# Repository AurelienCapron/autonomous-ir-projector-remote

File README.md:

# Télécommande Infrarouge Autonome pour Vidéoprojecteurs (Projet 32)

Conception matérielle (prototypage sur Arduino Uno puis PCB sur mesure sous KiCad 9), rétro-ingénierie de protocole infrarouge (standard NEC 38 kHz) et développement logiciel embarqué (MicroPython & C++) d'un boîtier autonome destiné à éteindre automatiquement les vidéoprojecteurs de la salle des conseils de **Grenoble INP - Phelma** lorsqu'elle est inoccupée. Ce système prévient l'usure prématurée des lampes (estimée à 1 250 h/an d'allumage inutile, soit 33 % de leur durée de vie) et réduit la consommation énergétique du bâtiment.

* **[Consulter le rapport technique du projet (PDF)](docs/project_report.pdf)**
* **[Consulter le support de soutenance technique (PDF)](docs/presentation_slides.pdf)**
* **[Consulter le schéma électrique du prototype initial (PDF)](docs/arduino_prototype_schematic.pdf)**
* **[Voir la vidéo de démonstration du prototype en salle des conseils](assets/autonomous_remote_demo.mp4?raw=true)**

---

## Sommaire
1. [Aperçu matériel : du prototype au produit final](#aperçu-matériel--du-prototype-au-produit-final)
2. [Contexte et cahier des charges (SysML)](#contexte-et-cahier-des-charges-sysml)
3. [Architecture matérielle et carte PCB (KiCad 9)](#architecture-matérielle-et-carte-pcb-kicad-9)
4. [Rétro-ingénierie du protocole NEC et firmware embarqué](#rétro-ingénierie-du-protocole-nec-et-firmware-embarqué)
5. [Conception mécanique et intégration du boîtier](#conception-mécanique-et-intégration-du-boîtier)
6. [Structure du dépôt](#structure-du-dépôt)
7. [Auteurs et encadrement](#auteurs-et-encadrement)

---

## Aperçu matériel : du prototype au produit final

| Phase 1 : Prototypage sur breadboard (Arduino Uno) | Phase 2 : Conception PCB sur mesure (KiCad 9 — v1.2) |
| :---: | :---: |
|  |  |
| *Câblage initial sur plaque d'essai : Arduino Uno, 2 capteurs PIR, 4 LDR (`A0`–`A3`), récepteur et LED IR* | *Carte finale double face accueillant le Raspberry Pi Pico 2WH, l'étage LDO 5V et les connecteurs dédiés* |

| Assemblage et soudure au laboratoire | Câblage interne dans le boîtier | Prototype final assemblé et testé |
| :---: | :---: | :---: |
|  |  |  |

---

## Contexte et cahier des charges (SysML)

À l'issue des réunions en salle des conseils, les vidéoprojecteurs restent fréquemment allumés toute la nuit (environ 2 fois par semaine, soit $1\,250\text{ h/an}$ sur une durée de vie totale de lampe de $3\,000$ à $4\,000\text{ h}$). Le système conçu répond à trois niveaux d'exigences fonctionnelles :
1. **Détection de l'état réel des vidéoprojecteurs :** Mesure directe de la tension sur les sorties **VGA** (`VGA1`, `VGA2`) couplée à des photorésistances (`PGM1201`) afin de ne commander l'extinction que si l'appareil ciblé est effectivement sous tension.
2. **Surveillance multi-capteurs de l'occupation :** Fusion des informations issues d'un capteur de mouvement infrarouge passif (`SBC-PIR`), d'un radar de présence à ondes millimétriques (`mmWave Gravity SEN0609`) et d'un détecteur acoustique (`SEN-14262`).
3. **Extinction automatique et mode *Sniffer* d'apprentissage :** Émission d'une salve infrarouge d'extinction après $1\text{h}30$ ($5\,400\text{ s}$) d'inactivité ou en cas de surchauffe/luminosité excessive, et possibilité de cloner à la volée une nouvelle télécommande par simple appui long (3 secondes) sur le bouton d'apprentissage (`GPIO19`).

---

## Architecture matérielle et carte PCB (KiCad 9)

### Brochage de la carte électronique (Version 1.2)

La carte électronique double face ($135 \times 130\text{ mm}$) intègre un étage de régulation linéaire **5V** (`TLV1117-50` alimenté en 12V DC via `J1`) et centralise l'ensemble des capteurs et actionneurs autour du microcontrôleur **Raspberry Pi Pico 2WH** :

| Connecteur PCB | Signal / Label | Broche MCU | Rôle fonctionnel |
|---|---|---|---|
| **`J_VGA1` / `J_VGA2`** | `VGA1` / `VGA2` | `GPIO3` / `GPIO2` | Lecture de l'état sous tension des vidéoprojecteurs 1 et 2 via leurs ports VGA. |
| **`J_Photoresistance1/2`** | `ADC0` / `ADC1` | `GPIO26` / `GPIO27` | Mesure analogique de luminosité (`PGM1201`) avec pont diviseur $10\text{ k}\Omega$ (`R5`, `R6`). |
| **`RV1`** | `ADC2` | `GPIO28` | Potentiomètre CMS Vishay `TS53YL` ($100\text{ k}\Omega$) d'ajustement dynamique du seuil. |
| **`J_DETECTEUR_MOUVEMENT1`** | `SIG` | `GPIO16` | Entrée numérique du capteur de mouvement infrarouge passif (`SBC-PIR`). |
| **`J_DETECTEUR_PRESENCE1`** | `VOUT` | `GPIO17` | Entrée numérique du capteur de présence radar mmWave (`SEN0609`). |
| **`J_CAPTEUR_SONORE1/2`** | `ENVELOPE` / `GATE` | `GPIO20` / `GPIO21` | Acquisition de l'enveloppe acoustique et du seuil binaire (`SEN-14262`). |
| **`J_EMETTEUR1` / `2`** | `EMETTEUR1` / `2` | `GPIO7` / `GPIO14` | Commande PWM 38 kHz des 2 émetteurs IR (`GT1087`) via résistances $220\ \Omega$ (`R3`, `R4`). |
| **`J_RECEPTEUR1`** | `S_OUT` | `GPIO18` | Réception et apprentissage (*Sniffer*) de trames infrarouges externes (`GT1089`). |
| **`J_Bouton1`** | `BOUTON` | `GPIO19` | Bouton poussoir (`R1381R`, `PULL_UP`) activant le mode apprentissage après 3 s d'appui. |
| **`J_LED1` / `J_LED2`** | `Net-(GPIO0/1)` | `GPIO0` / `GPIO1` | LED témoins en façade (Présence détectée sur `GPIO0`, Projecteur allumé sur `GPIO1`). |

### Nomenclature matérielle (BOM)

| Composant | Référence | Quantité | Fonction |
|---|---|---|---|
| Microcontrôleur | `Raspberry Pi Pico 2WH` (`SC1634`) | 1 | Unité centrale de traitement, PWM 38 kHz et machine d'état |
| Régulateur LDO 5V | `TLV1117-50` (SOT-223) | 1 | Régulation 12V → 5V (`VCC`) avec condensateurs CMS $10\ \mu\text{F}$ (`C1`, `C2`) |
| Détecteur sonore | `SEN-14262` | 1 | Surveillance de l'activité sonore dans la salle des conseils |
| Radar de présence | `mmWave Gravity SEN0609` | 1 | Détection fine de présence humaine statique ou en mouvement |
| Capteur PIR | `SBC-PIR` | 1 | Détection de mouvement thermique dans la salle |
| Photorésistances | `PGM1201` | 4 | Détection optique complémentaire et sécurité de surchauffe |
| Émetteurs IR | `GT1087` | 2 | Émission directionnelle des trames d'extinction à 38 kHz |
| Récepteur IR | `GT1089` | 1 | Capture et clonage du signal de la télécommande d'origine |
| Bouton poussoir | `R1381R` | 1 | Déclenchement manuel du mode d'apprentissage infrarouge |

---

## Rétro-ingénierie du protocole NEC et firmware embarqué

### 1. Identification et décodage de la trame à l'oscilloscope
Le signal émis par la télécommande d'origine face au récepteur `GT1089` a été capturé à l'oscilloscope numérique **Tektronix** et décodé via un banc Arduino Uno (`firmware/arduino_ir_receiver`), révélant une modulation **NEC** sur porteuse à **38 kHz** de valeur hexadécimale brute **`0x6F905583`** (soit les 4 octets `0x83`, `0x55`, `0x90`, `0x6F` transmis LSB-first) :

* **En-tête de synchronisation (AGC Burst) :** Impulsion modulée de $9\text{ ms}$ (`mark(9000)`) suivie d'un silence de $4,5\text{ ms}$ (`space(4500)`).
* **Bit logique `0` :** Impulsion de $562\ \mu\text{s}$ suivie d'un silence de $562\ \mu\text{s}$ (durée totale : $1,125\text{ ms}$).
* **Bit logique `1` :** Impulsion de $562\ \mu\text{s}$ suivie d'un silence long de $1,675\ \text{ms}$ (durée totale : $2,25\text{ ms}$).

| Principe temporel du protocole NEC | Capture de la trame IR à l'oscilloscope Tektronix |
| :---: | :---: |
|  |  |

### 2. Synthèse PWM 38 kHz et mode *Sniffer* sous MicroPython (`firmware/pico_main/main.py`)
Le firmware principal embarqué sur le **Raspberry Pi Pico 2WH** pilote simultanément les deux émetteurs IR (`GPIO7` et `GPIO14`) via les générateurs PWM matériels cadencés à $38\text{ kHz}$ (rapport cyclique de 50 %, `duty_u16(32768)`) :
* **Triple tir d'extinction (`envoyer_code_nec_universel()`) :** Envoie 3 trames NEC consécutives espacées de $500\text{ ms}$ pour garantir la prise en compte de l'extinction (y compris sur les projecteurs exigeant une double confirmation).
* **Mode d'apprentissage universel (`lancer_mode_apprentissage()`) :** Un appui de plus de 3 secondes sur le bouton `GPIO19` place le boîtier en écoute sur le récepteur `GT1089` (`GPIO18`), mesure à la microseconde les 67 fronts successifs (`time.ticks_us()`), discrimine les bits `1` ($> 1\,200\ \mu\text{s}$) et `0`, et met à jour dynamiquement en mémoire les 4 octets `NEC_B1` à `NEC_B4`.

---

## Conception mécanique et intégration du boîtier

Pour protéger la carte électronique de la poussière dans le faux plafond tout en intégrant les passages de câbles et l'interface utilisateur :
1. **Modélisation 3D initiale (CAO 3D) :** Conception d'un boîtier perforé et de son couvercle à poignée.
2. **Boîtier en bois découpé au laser (solution retenue) :** Conception d'un boîtier assemblé à créneaux ($14 \times 15,5 \times 10\text{ cm}$) généré via `boxes.py`, adapté en CAO 2D pour les perçages des connecteurs et fabriqué au FabLab de Phelma.

| Modélisation 3D de la base | Modélisation 3D du couvercle | Plan 2D de découpe laser (`boxes.py`) |
| :---: | :---: | :---: |
|  |  |  |

| Banc de démonstration lors de la soutenance finale |
| :---: |
|  |

---

## Structure du dépôt

```text
autonomous-ir-projector-remote/
├── .gitattributes                            # Détection KiCad / Python / C++ par GitHub Linguist
├── .gitignore
├── README.md
├── assets/
│   ├── arduino_breadboard_prototype.png      # Câblage du prototype initial sur breadboard (Tinkercad)
│   ├── autonomous_remote_demo.mp4            # Vidéo de test d'extinction automatique en salle
│   ├── enclosure_3d_base.jpg                 # Modélisation CAO 3D du boîtier
│   ├── enclosure_3d_lid.jpg                  # Modélisation CAO 3D du couvercle
│   ├── ir_frame_oscilloscope.png             # Acquisition Tektronix de la trame NEC 32 bits
│   ├── laser_cut_layout.jpg                  # Mise à plat 2D pour découpe laser
│   ├── nec_protocol_timing.png               # Chronogramme du protocole NEC
│   ├── pcb_3d_render.png                     # Rendu 3D de la carte PCB sous KiCad 9 (v1.2)
│   ├── pcb_soldering_bench.jpg               # Assemblage et soudure de la carte au laboratoire
│   ├── project_defense_setup.jpg             # Démonstration lors de la soutenance
│   ├── prototype_assembled_box.png           # Boîtier final assemblé et câblé
│   ├── prototype_inside_wiring.png           # Vue intérieure du câblage (Raspberry Pi Pico 2WH)
│   ├── sysml_requirements_diagram.png        # Diagramme des exigences SysML
│   └── system_architecture.svg               # Schéma synoptique vectoriel de l'architecture
├── docs/
│   ├── arduino_prototype_schematic.pdf       # Premier schéma électrique sur Arduino Uno
│   ├── bom_components.csv                    # Nomenclature initiale des composants (CSV)
│   ├── presentation_slides.pdf               # Support de soutenance technique
│   └── project_report.pdf                    # Rapport technique du projet (Grenoble INP - Phelma)
├── firmware/
│   ├── arduino_ir_receiver/
│   │   └── arduino_ir_receiver.ino           # Capture et décodage hexadécimal de la trame NEC
│   ├── arduino_ir_sender/
│   │   └── arduino_ir_sender.ino             # Test d'émission du code 0x6F905583 sous Arduino
│   └── pico_main/
│       └── main.py                           # Firmware complet MicroPython (capteurs, NEC, Sniffer)
└── hardware_kicad/
    ├── BE-Elec-Projet-Type-Kicad.kicad_pro   # Projet KiCad 9.0
    ├── BE-Elec-Projet-Type-Kicad.kicad_sch   # Schéma électrique complet
    └── BE-Elec-Projet-Type-Kicad.kicad_pcb   # Routage PCB double face (Version 1.2)
```

---

## Auteurs et encadrement

Projet réalisé à **Grenoble INP - Phelma** (Année universitaire 2025–2026 — Projet n°32) :
* **Équipe Partie II (Télécommande autonome) :** Aurélien Capron (Chef de projet), Amaury Simonnot, Corentin Pilleux, Corentin Eletti, Reda Lounis.
* **Équipe Partie I (Interface PWM / S.Bus) :** Martin Fleury, Mathis Menager, Jules Ancel, Simon Danquigny.
* **Encadrement :** Julien Traveaux, Sophie Cornu et l'équipe du FabLab de Grenoble INP - Phelma.

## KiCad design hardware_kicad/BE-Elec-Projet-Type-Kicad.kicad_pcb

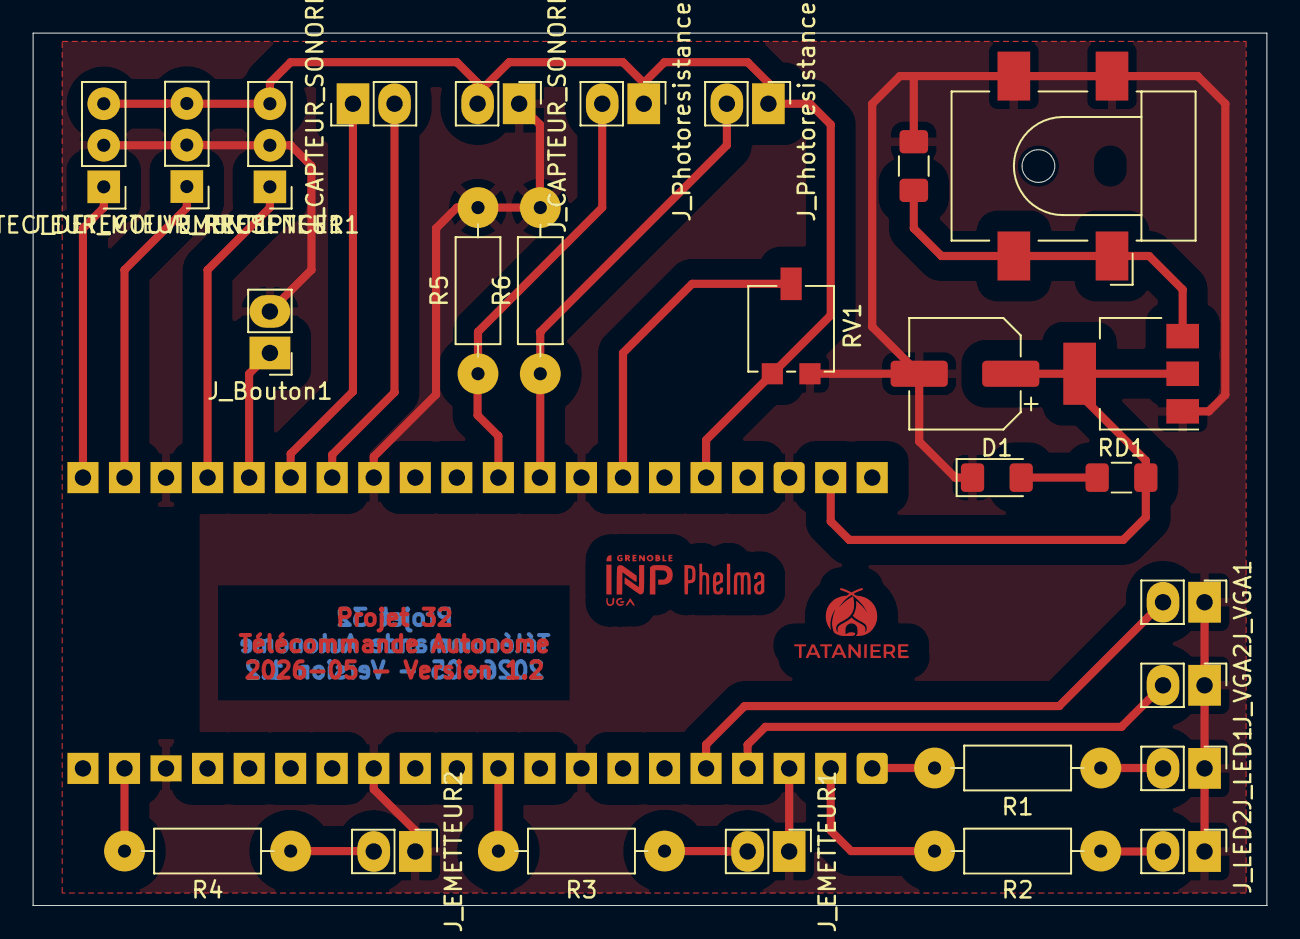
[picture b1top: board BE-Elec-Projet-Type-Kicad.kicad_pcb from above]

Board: 2 copper layers, 75.4 x 53.3 mm, 29 parts (1 on the bottom side), 24 nets.

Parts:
A1: RaspberryPi_Pico_W; RaspberryPi_Pico_Common_THT
C1: 10u; C_1206_3216Metric_Pad1.42x1.75mm_HandSolder
C2: 10u; CP_Elec_6.3x5.2
D1: LED; LED_1206_3216Metric_Pad1.42x1.75mm_HandSolder
G: LOGO; tata
J1: Barrel_Jack_Switch; BarrelJack_CLIFF_FC681465S_SMT_Horizontal
J_Bouton1: Conn_01x02; PinHeader_1x02_P2.54mm_Vertical
J_CAPTEUR_SONORE1, J_CAPTEUR_SONORE2: Conn_01x02; PinHeader_1x02_P2.54mm_Vertical
J_DETECTEUR_MOUVEMENT1: Conn_01x03; PinHeader_1x03_P2.54mm_Vertical
J_DETECTEUR_PRESENCE1: Conn_01x03; PinHeader_1x03_P2.54mm_Vertical
J_EMETTEUR1, J_EMETTEUR2: Conn_01x02; PinHeader_1x02_P2.54mm_Vertical
J_LED1, J_LED2: Conn_01x02; PinHeader_1x02_P2.54mm_Vertical
J_Photoresistance1, J_Photoresistance2: Conn_01x02; PinHeader_1x02_P2.54mm_Vertical
J_RECEPTEUR1: Conn_01x03; PinHeader_1x03_P2.54mm_Vertical
J_VGA1, J_VGA2: Conn_01x02; PinHeader_1x02_P2.54mm_Vertical
R1, R2, R3, R4: 220; R_Axial_DIN0207_L6.3mm_D2.5mm_P10.16mm_Horizontal
R5, R6: 10k; R_Axial_DIN0207_L6.3mm_D2.5mm_P10.16mm_Horizontal
RD1: 470; R_1206_3216Metric_Pad1.42x1.75mm_HandSolder
RV1: 100K; Potentiometer_Vishay_TS53YL_Vertical
U1: TLV1117-50; SOT-223-3_TabPin2

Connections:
3V3: A1.36 (3V3), J_CAPTEUR_SONORE1.2, J_DETECTEUR_MOUVEMENT1.3, J_DETECTEUR_PRESENCE1.3, J_Photoresistance1.1, J_Photoresistance2.1, J_RECEPTEUR1.3, RV1.3
+12V: C1.1, J1.1, U1.3 (VI)
BOUTON: A1.25 (GPIO19), J_Bouton1.1
EMETTEUR1: A1.10 (GPIO7), R3.2
EMETTEUR2: A1.19 (GPIO14), R4.2
ENVELOPE: A1.26 (GPIO20), J_CAPTEUR_SONORE2.1
GATE: A1.27 (GPIO21), J_CAPTEUR_SONORE2.2
GND: A1.3 (GND), A1.8 (GND), A1.13 (GND), A1.18 (GND), A1.23 (GND), A1.28 (GND), A1.33 (AGND), A1.38 (GND), C1.2, C2.2, D1.1 (K), J1.2, J1.3, J_Bouton1.2, J_CAPTEUR_SONORE1.1, J_DETECTEUR_MOUVEMENT1.2, J_DETECTEUR_PRESENCE1.2, J_EMETTEUR1.1, J_EMETTEUR2.1, J_LED1.1, J_LED2.1, J_RECEPTEUR1.2, J_VGA1.1, J_VGA2.1, R5.2, R6.2, RV1.1, U1.1 (GND)
unnamed: A1.1 (GPIO0), R1.2
unnamed: A1.2 (GPIO1), R2.2
unnamed: A1.31 (GPIO26_ADC0), J_Photoresistance1.2, R5.1
unnamed: A1.32 (GPIO27_ADC1), J_Photoresistance2.2, R6.1
unnamed: A1.34 (GPIO28_ADC2), RV1.2
unnamed: D1.2 (A), RD1.1
unnamed: J_EMETTEUR1.2, R3.1
unnamed: J_EMETTEUR2.2, R4.1
unnamed: J_LED1.2, R1.1
unnamed: J_LED2.2, R2.1
SIG: A1.21 (GPIO16), J_DETECTEUR_MOUVEMENT1.1
S_OUT: A1.24 (GPIO18), J_RECEPTEUR1.1
VCC: A1.39 (VSYS), C2.1, RD1.2, U1.2 (VO)
VGA1: A1.5 (GPIO3), J_VGA1.2
VGA2: A1.4 (GPIO2), J_VGA2.2
VOUT: A1.22 (GPIO17), J_DETECTEUR_PRESENCE1.1
